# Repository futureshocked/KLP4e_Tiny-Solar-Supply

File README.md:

# KLP4e_Tiny-Solar-Supply

This is the repository for the "Tiny Solar Supply" project.

This is one of the projects from the course [KiCad Like a Pro, 4th edition](https://techexplorations.com/so/kicad-like-a-pro-4th-edition).

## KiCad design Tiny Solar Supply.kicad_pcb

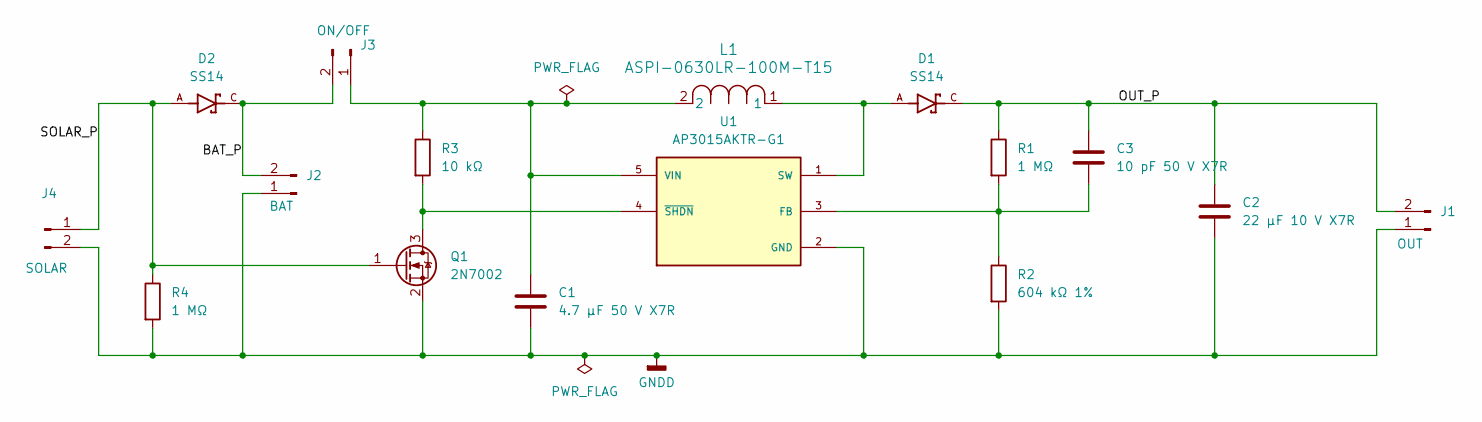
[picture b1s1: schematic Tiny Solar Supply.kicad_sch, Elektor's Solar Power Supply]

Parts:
C1: 4.7 μF 50 V X7R; C_0805_2012Metric
C2: 22 μF 10 V X7R; C_1206_3216Metric
C3: 10 pF 50 V X7R; C_0805_2012Metric
D1, D2: SS14; DIOM4325X250N; PARTREV O2102
J1, J2, J3: Conn_01x02_Pin; PinHeader_1x02_P2.54mm_Vertical
J4: Conn_01x02_Pin; PinHeader_1x02_P2.00mm_Horizontal
L1: ASPI-0630LR-100M-T15; IND_ASPI-0630LR_ABR
Q1: 2N7002; SOT-23
R1, R4: 1 ΜΩ; R_0805_2012Metric
R2: 604 kΩ 1%; R_0805_2012Metric
R3: 10 kΩ; R_0805_2012Metric
U1: AP3015AKTR-G1; SOT95P280X145-5N; PARTREV 1.4

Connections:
/BAT_P: D2.C, J2.2, J3.2
/OUT_P: C2.1, C3.1, D1.C, J1.2, R1.1
/SOLAR_P: D2.A, J4.1, Q1.1 (G), R4.1
GNDD: C1.2, C2.2, J1.1, J2.1, J4.2, Q1.2 (S), R2.2, R4.2, U1.2 (GND)
unnamed: C1.1, J3.1, L1.2, R3.1, U1.5 (VIN)
unnamed: Q1.3 (D), R3.2, U1.4 (~SHDN)
unnamed: C3.2, R1.2, R2.1, U1.3 (FB)
unnamed: D1.A, L1.1, U1.1 (SW)

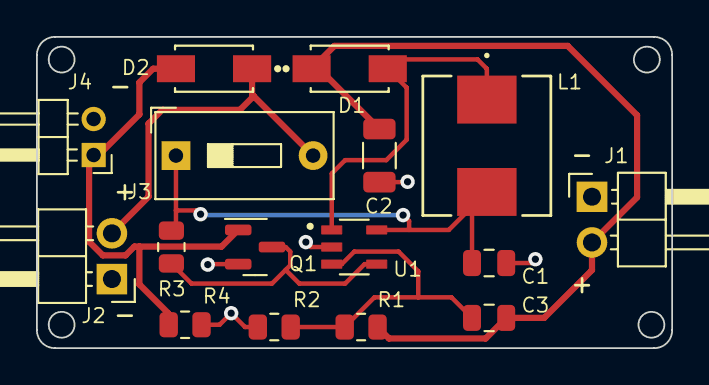
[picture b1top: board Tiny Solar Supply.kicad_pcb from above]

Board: 2 copper layers, 35.3 x 17.3 mm, 16 parts (0 on the bottom side), 8 nets.
